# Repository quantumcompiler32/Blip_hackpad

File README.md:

# Blip

Blip is a custom macropad I am designing for macOS. It combines a 4-row by
3-column mechanical-key matrix, two rotary encoders, a XIAO ESP32-S3, and two
displays. The goal is to make a small physical control surface that can trigger
useful actions and show status without feeling like a tiny touchscreen.

## Features

- 12-key (3x4) mechanical switch matrix
- 1N4148 diode matrix for anti-ghosting
- Seeed Studio XIAO ESP32-S3 controller for native USB HID
- MCP23017 I2C GPIO expander for additional IO
- Newhaven 20x4 character OLED display
- Two rotary encoders with push switches
- USB-C-only power through the removable XIAO module
- A removable MCP23017 GPIO expander and removable display connections

## Bill of materials

The full, quoted CSV is in [`BOM/Hackpad_final_BOM.csv`](./BOM/Hackpad_final_BOM.csv).
It matches the current PCB: 12 keys, 12 diodes, two encoders, two 4.7 kΩ
pull-ups, one 100 nF capacitor, the XIAO ESP32-S3, the MCP23017, and both
display modules. The removable socket and header parts are listed separately
because they are assembly parts rather than separate KiCad footprints.

The current component total is **$97.95 USD** using the listed prices. That
number does not include PCB fabrication, an enclosure, keycaps, encoder knobs,
or mounting hardware. Prices are planning numbers, not a final purchase quote.

## Repository Structure

```text
Blip_hackpad/
├── BOM/                Bill of materials
├── Images/             Schematic and PCB reference images
├── PCB/                KiCad design files and manufacturing outputs
├── docs/               Architecture, specifications, and validation evidence
├── src/
│   ├── blip-agent/     Background host event pipeline
│   ├── control-center/ Minimal diagnostic view
│   ├── firmware/       Complete PlatformIO project
│   ├── shared/         Device-event and semantic-state contracts
│   └── simulator/      Virtual Blip Device and scenario CLI
└── test/               Foundation acceptance tests
```

## Hardware submission status

The KiCad project in `PCB/` is the hardware source of truth. Automated ERC,
DRC, schematic-parity, source-policy, and BOM checks are recorded in
`docs/hardware/`. The Hardware Validation Gate is not a manufacturing approval:
I still need to inspect the current STEP export, confirm connector and encoder
clearances with the real parts, review USB-C access, and sign the final
manufacturing checklist in [`docs/hardware/hardware-change-guide.md`](./docs/hardware/hardware-change-guide.md).
The complete repository-versus-Macondo checklist is in
[`docs/hardware/macondo-submission-checklist.md`](./docs/hardware/macondo-submission-checklist.md).

To rerun the repository checks:

```sh
sh scripts/verify-hardware-source-of-truth.sh
sh scripts/verify-minimal-pcb-corrections.sh
sh scripts/verify-bom-against-pcb.sh
sh scripts/verify-hardware-validation-gate.sh
```

## Simulator tracer scenario

Node.js 22.6 or newer can run the Foundation tracer without installing
dependencies:

```sh
npm test
npm run --silent scenario
npm run --silent scenario:view > /tmp/blip-control-center-diagnostic.html
```

The scenario command emits machine-readable JSON. The HTML command renders the
same Agent observation as a minimal Control Center diagnostic view. Both outputs
label the device as virtual, and the scenario never executes a host action.

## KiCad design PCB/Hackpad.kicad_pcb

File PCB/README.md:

# Blip PCB source of truth

The three `Hackpad.kicad_*` files in this directory are the authoritative revision-one KiCad project. They were migrated unchanged from Moksh's active project on 2026-07-18.

Do not commit KiCad locks, automatic backups, local preferences, history folders, cached footprint data, or the unrelated Starter project. Hardware corrections must be made to these sources and documented in the Hardware Change Guide.

Run `sh scripts/verify-hardware-source-of-truth.sh` to verify the durable source policy. The migration hashes are historical evidence in the baseline findings; they are intentionally not enforced after approved PCB edits. A passing source-policy check does not mean the Hardware Validation Gate has passed.

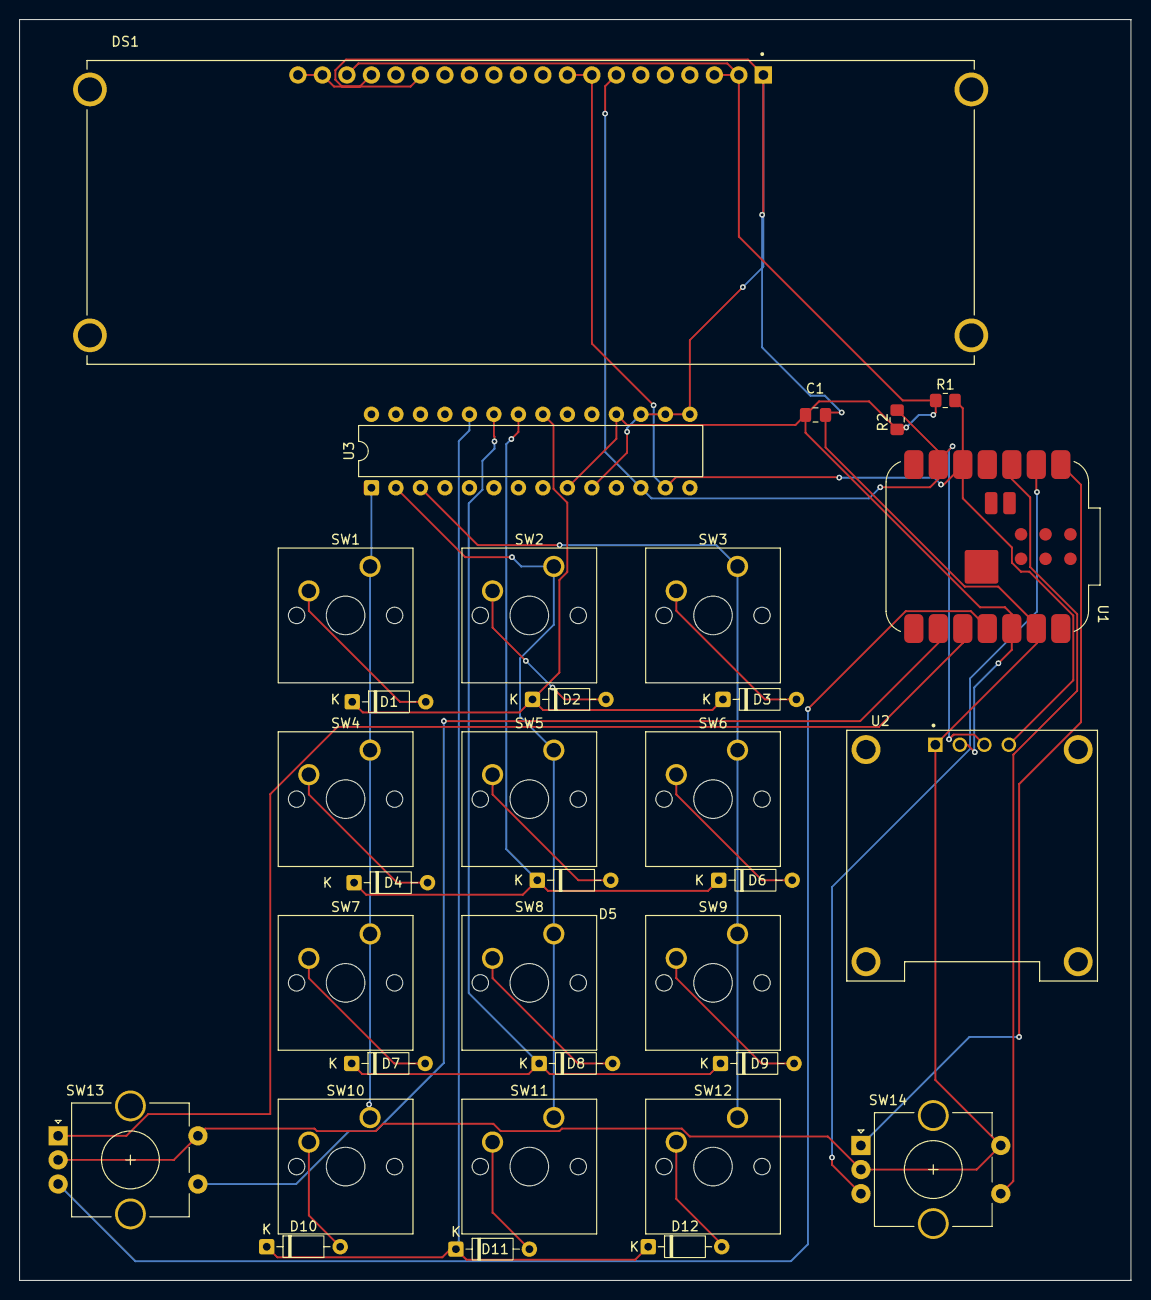
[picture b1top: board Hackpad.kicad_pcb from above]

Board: 2 copper layers, 115.2 x 130.8 mm, 33 parts (0 on the bottom side), 29 nets.

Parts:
C1: 100nF; C_0805_2012Metric_Pad1.18x1.45mm_HandSolder
D1, D2, D3, D4, D5, D6, D7, D8, D9, D10, D11, D12: 1N4148; D_DO-35_SOD27_P7.62mm_Horizontal
DS1: NHD-0420CW-AB3; LCD_NHD-0420CW-AB3
R1, R2: 4.7k; R_0805_2012Metric_Pad1.20x1.40mm_HandSolder
SW1, SW2, SW3, SW4, SW5, SW6, SW7, SW8, SW9, SW10, SW11, SW12: SW_Cherry_MX_1.00u_PCB
SW13, SW14: RotaryEncoder_Switch; RotaryEncoder_Alps_EC11E-Switch_Vertical_H20mm_CircularMoun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
U1: MOUDLE-SEEEDUINO-XIAO; MCU_Seeed_ESP32C3
U2: DM-OLED096-636; MODULE_DM-OLED096-636
U3: MCP23017x-x-SP; DIP-28_W7.62mm

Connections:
+3.3V: C1.1, DS1.2 (VDD), DS1.3 (REGVDD), DS1.18 (BS1), R1.1, R2.1, U1.12 (3V3), U2.2 (VCC_IN), U3.9 (V_{DD}), U3.18 (~RESET)
/COL0: SW1.1, SW4.1, SW7.1, SW10.1, U3.1 (GPB0)
/COL1: SW2.1, SW5.1, SW8.1, SW11.1, U3.2 (GPB1)
/COL2: SW3.1, SW6.1, SW9.1, SW12.1, U3.3 (GPB2)
/ENC_A: SW13.A, U1.10 (PA5_A9_D9_MISO)
/ENC_B: SW13.B, U1.11 (PA6_A10_D10_MOSI)
/ENC_C: SW14.A, U1.1 (PA02_A0_D0)
/ENC_D: SW14.B, U1.2 (PA4_A1_D1)
/ENC_SW: SW13.S1, U1.9 (PA7_A8_D8_SCK)
/ENC_SW1: SW14.S1, U1.3 (PA10_A2_D2)
/ROW0: D1.1 (K), D2.1 (K), D3.1 (K), U3.21 (GPA0)
/ROW1: D4.1 (K), D5.1 (K), D6.1 (K), U3.22 (GPA1)
/ROW2: D7.1 (K), D8.1 (K), D9.1 (K), U3.23 (GPA2)
/ROW3: D10.1 (K), D11.1 (K), D12.1 (K), U3.24 (GPA3)
/SCL: DS1.7 (DB0/SCLK/SCL), R2.2, U1.6 (PA9_A5_D5_SCL), U2.3 (SCL), U3.12 (SCK)
/SDA: DS1.8 (DB1/SDI/SDAIN), DS1.9 (DB2/SDO/SDAOUT), R1.2, U1.5 (PA8_A4_D4_SDA), U2.4 (SDA), U3.13 (SDA)
GND: C1.2, DS1.1 (VSS), DS1.15 (~CS/NC), DS1.17 (BS0), DS1.19 (BS2), DS1.20 (VSS), SW13.C, SW13.S2, SW14.C, SW14.S2, U1.13 (GND), U2.1 (GND), U3.10 (V_{SS}), U3.15 (A0), U3.16 (A1), U3.17 (A2)
unnamed: D1.2 (A), SW1.2
unnamed: D2.2 (A), SW2.2
unnamed: D3.2 (A), SW3.2
unnamed: D4.2 (A), SW4.2
unnamed: D5.2 (A), SW5.2
unnamed: D6.2 (A), SW6.2
unnamed: D7.2 (A), SW7.2
unnamed: D8.2 (A), SW8.2
unnamed: D9.2 (A), SW9.2
unnamed: D10.2 (A), SW10.2
unnamed: D11.2 (A), SW11.2
unnamed: D12.2 (A), SW12.2
